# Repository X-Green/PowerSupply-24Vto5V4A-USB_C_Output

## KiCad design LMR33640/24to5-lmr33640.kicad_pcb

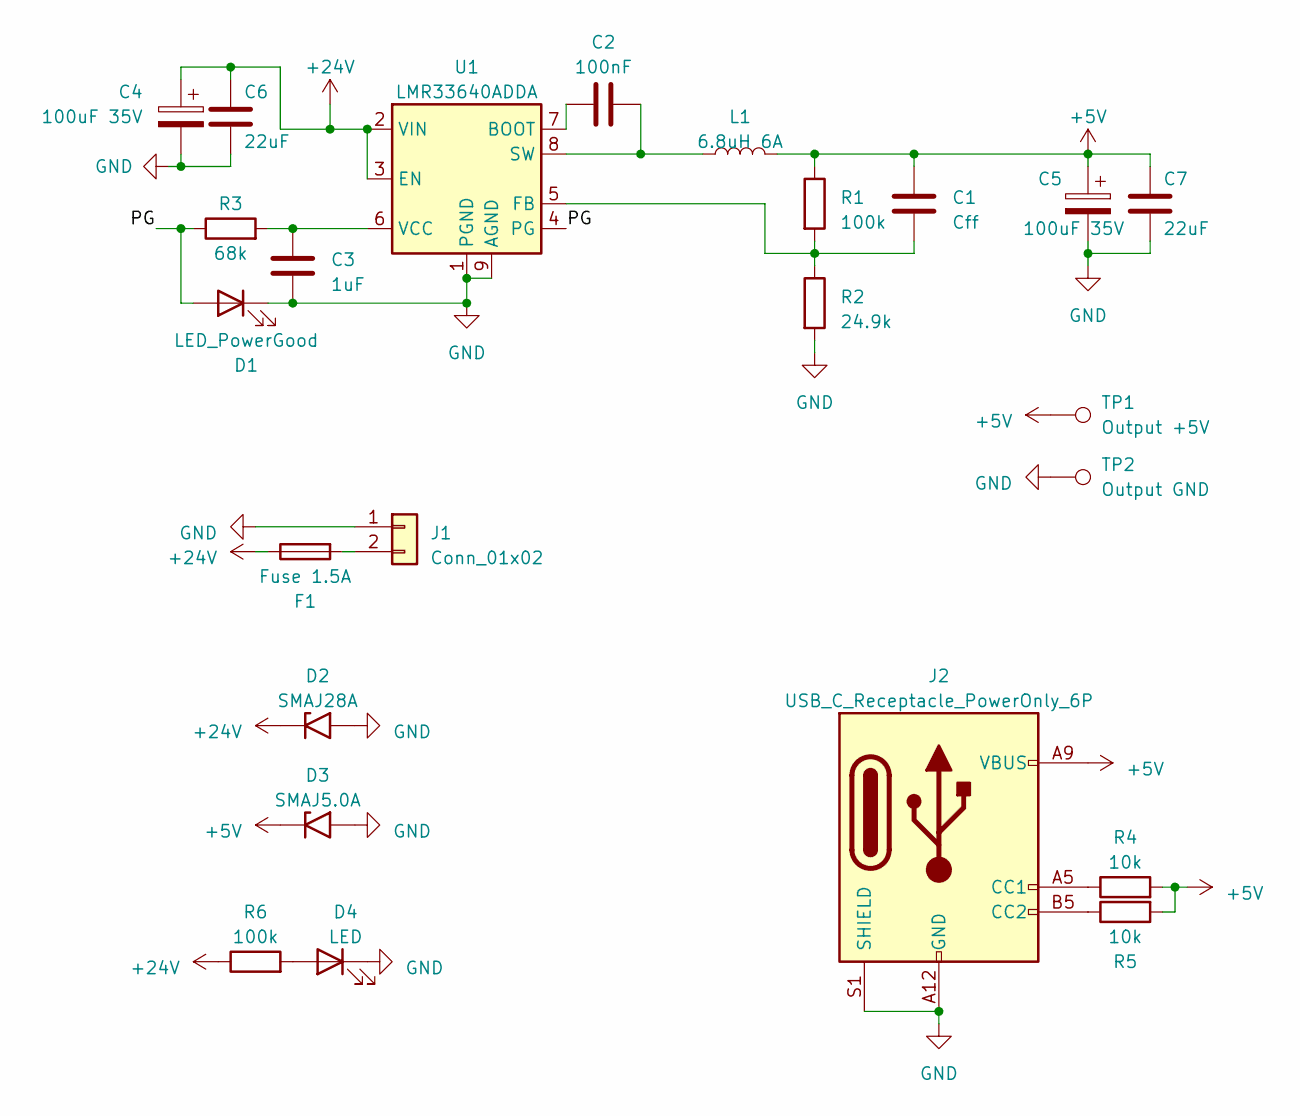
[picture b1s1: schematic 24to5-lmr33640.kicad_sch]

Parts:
C1: Cff; C_0603_1608Metric
C2: 100nF; C_0603_1608Metric
C3: 1uF; C_0603_1608Metric
C4, C5: 100uF 35V; CP_Radial_D6.3mm_P2.50mm
C6, C7: 22uF; C_1206_3216Metric
D1: LED_PowerGood; LED_0603_1608Metric
D2: SMAJ28A; D_SMA
D3: SMAJ5.0A; D_SMA
D4: LED; LED_0603_1608Metric
F1: Fuse 1.5A; Fuse_1812_4532Metric
J1: Conn_01x02; AMASS_XT30U-M_1x02_P5.0mm_Vertical
J2: USB_C_Receptacle_PowerOnly_6P; TYPEC31M17
L1: 6.8uH 6A; L_Sunlord_MWSA0603S
R1, R6: 100k; R_0603_1608Metric
R2: 24.9k; R_0603_1608Metric
R3: 68k; R_0603_1608Metric
R4, R5: 10k; R_0603_1608Metric
TP1: Output +5V; TestPoint_Plated_Hole_D2.0mm
TP2: Output GND; TestPoint_Plated_Hole_D2.0mm
U1: LMR33640ADDA; Texas_HSOP-8-1EP_3.9x4.9mm_P1.27mm_ThermalVias

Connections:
+5V: C1.1, C5.1, C7.1, D3.1 (A1), J2.A9 (VBUS), J2.B9 (VBUS), L1.2, R1.1, R4.2, R5.2, TP1.1
+24V: C4.1, C6.1, D2.1 (A1), F1.1, R6.1, U1.2 (VIN), U1.3 (EN)
/PG: D1.2 (A), R3.1, U1.4 (PG)
GND: C3.2, C4.2, C5.2, C6.2, C7.2, D1.1 (K), D2.2 (A2), D3.2 (A2), D4.1 (K), J1.1, J2.A12 (GND), J2.B12 (GND), J2.S1 (SHIELD), R2.2, TP2.1, U1.1 (PGND), U1.9 (AGND)
unnamed: D4.2 (A), R6.2
unnamed: F1.2, J1.2
unnamed: J2.A5 (CC1), R4.1
unnamed: J2.B5 (CC2), R5.1
unnamed: C2.1, U1.7 (BOOT)
unnamed: C1.2, R1.2, R2.1, U1.5 (FB)
unnamed: C2.2, L1.1, U1.8 (SW)
unnamed: C3.1, R3.2, U1.6 (VCC)

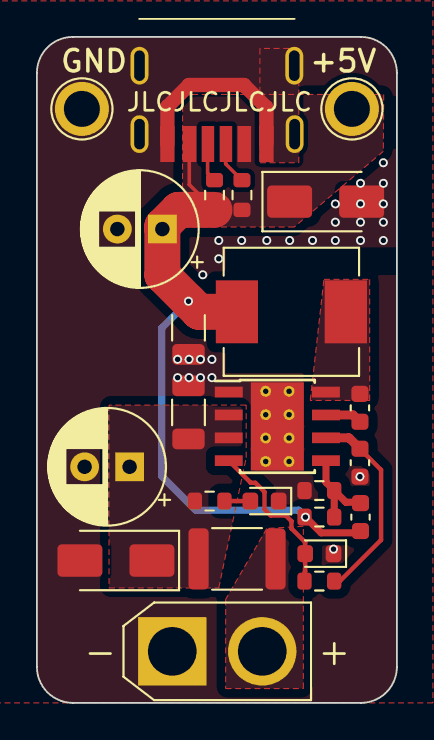
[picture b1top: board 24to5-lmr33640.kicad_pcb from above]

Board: 2 copper layers, 20.0 x 37.0 mm, 24 parts (0 on the bottom side), 12 nets.

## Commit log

2023-06-23 init
2023-06-23 layout done
2023-06-25 decoration
